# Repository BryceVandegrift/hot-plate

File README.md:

# PCB Hot Plate

A modular PCB soldering hot plate using only through hole components

## About

A modular PCB hot plate designed for hot plate soldering. It is designed for SMD
soldering and can go up to 180°C. Made using only through hole components in
order to make it easy to be built by hobbyists.

## Specifications

- 180°C max temperature
- Microcontroller: Atmel ATTINY84A
- Display: 128x64 pixel SSD1306 or compatible display
- Modular/interchangeable hot plates
- Support for simple heat curves
- 18-20 volt 2x5.5mm DC input
- 3 button input

Best used with low melt solder paste. This includes (but is not limited to):
- Sn48/In52
- Sn42/Bi58
- Sn42/Bi57/Ag1.0

## Usage

When you power up the hot plate you will be presented with 2 modes:

- Normal heating
- Heat curve

### Normal Heating

Normal heating mode is very simple to use. Just set a temperature and the hot
plate will heat up and stay at the set temperature. You can press `Enter` in
order to enter into cooling mode afterwards.

### Heat Curve

Heat curve mode lets you set and use your own custom heat curve. There are 5
parts to heat curve mode:

- Preheat: Temperature to preheat
- Soak: Amount of time (in seconds) to "soak" in preheat temperature
- Reflow heating: Temperature to reflow
- Reflow: Amount of time (in seconds) to reflow
- Cooldown

Pressing `Enter` will skip to the next stage of the heat curve.
Heat curve mode roughly follows this graph:

## Hardware

### Schematics

[Control Board Schematic](KiCAD/schematics/plate.pdf)

[Hot Plate Schematic](KiCAD/schematics/100x100-plate.pdf)

### Build Instructions

Please refer to the [Building Instructions](Build.md) page for detailed instructions.

### Connectors and Switches

#### J1 - DC Power Input

| Pin | Description   |
| --- | -----------   |
| 1   | +18-20V power |
| 2   | Ground        |
| 3   | Ground        |

#### J2 - ISCP Header

| Pin | Description  |
| --- | -----------  |
| 1   | MISO         |
| 2   | +5V          |
| 3   | SCL          |
| 4   | MOSI         |
| 5   | Reset        |
| 6   | Ground       |

#### J3 - Hot Plate Connector

| Pin | Description         |
| --- | -----------         |
| 1   | NC                  |
| 2   | +18-20V             |
| 3   | +18-20V             |
| 4   | MOSFET drain        |
| 5   | MOSFET drain        |
| 6   | +5V                 |
| 7   | Ground              |
| 8   | Temp. sensor output |

*Note: The J3 connector on the control board is exactly the same as the J1
connector on the hot plate board*

### Bill of Materials

A list of all Digikey parts can be found [here](https://www.digikey.com/en/mylists/list/93WA87OA5L)

#### Control Board

| Type               | Reference | Description                             | Quantity | Source                              |
| ----               | --------- | -----------                             | -------- | ------                              |
| Integrated Circuit | U1        | L7805CV voltage regulator               | 1        | Digikey 497-1443-5-ND               |
| Integrated Circuit | U2        | ATTINY84A-PU microcontroller            | 1        | Digikey ATTINY84A-PU-ND             |
| Display            | U3        | SSD1306 128x64 0.96" display            | 1        | Ebay, AliExpress, and other sources |
| IC Socket          | U2        | DIP-14 300 mil socket                   | 1        | Digikey ED3014-ND                   |
| Diode              | D1, D2    | SD103A                                  | 2        | Digikey SD103AVSCT-ND               |
| Diode              | D3        | 1N5231                                  | 1        | Digikey 1N5231B-ND                  |
| MOSFET             | Q1        | IRLZ44N                                 | 1        | Digikey IRLZ44NPBF-ND               |
| Capacitor          | C1        | 100uF, Electrolytic, 3.5mm lead spacing | 1        | Digikey 732-9187-1-ND               |
| Capacitor          | C2-C4, C8 | 0.1uF, MLCC, 5mm lead spacing           | 4        | Digikey BC2665CT-ND                 |
| Capacitor          | C5-C7     | 3300pF, MLCC, 2.5mm lead spacing        | 3        | Digikey BC1075CT-ND                 |
| Resistor           | R1-R5, R7 | 10kOhm, through hole                    | 6        | Digikey 13-MFR-25FRF52-10KCT-ND     |
| Resistor           | R6        | 30kOhm, through hole                    | 1        | Digikey 13-MFR-25FTE52-30KCT-ND     |
| Resistor           | R8        | 200Ohm, throught hole                   | 1        | Digikey 200XBK-ND                   |
| Tactile Button     | SW1-SW3   | 6mm tactile button                      | 3        | Digikey 450-1654-ND                 |
| DC Jack            | J1        | 2x5.5mm, through hole, right angle      | 1        | Digikey CP-002AH-ND                 |
| Pin Header         | J2        | 6 pin header, 2.54mm pitch, 2x3 pins    | 1        | Digikey 732-5394-ND                 |
| Pin Header         | J3        | 8 pin header, 2.54mm pitch, right angle | 1        | Digikey 2057-PH1RB-08-UA-ND         |

#### Hot Plate

| Type               | Reference | Description                             | Quantity | Source                             |
| ----               | --------- | -----------                             | -------- | ------                             |
| Integrated Circuit | U1        | LMT87LPGM temperature sensor            | 1        | Digikey 296-LMT87LPGMCT-ND         |
| Capacitor          | C1, C2    | 0.1uF, MLCC, 5mm lead spacing           | 2        | Digikey BC2665CT-ND                |
| Pin Socket         | J1        | 8 pin header, 2.54mm pitch, right angle | 1        | Digikey S5483-ND                   |

## License

Source code is licensed under the GPLV3 or later.

Everything else is licensed under the CERN-OHL-W-2.0.

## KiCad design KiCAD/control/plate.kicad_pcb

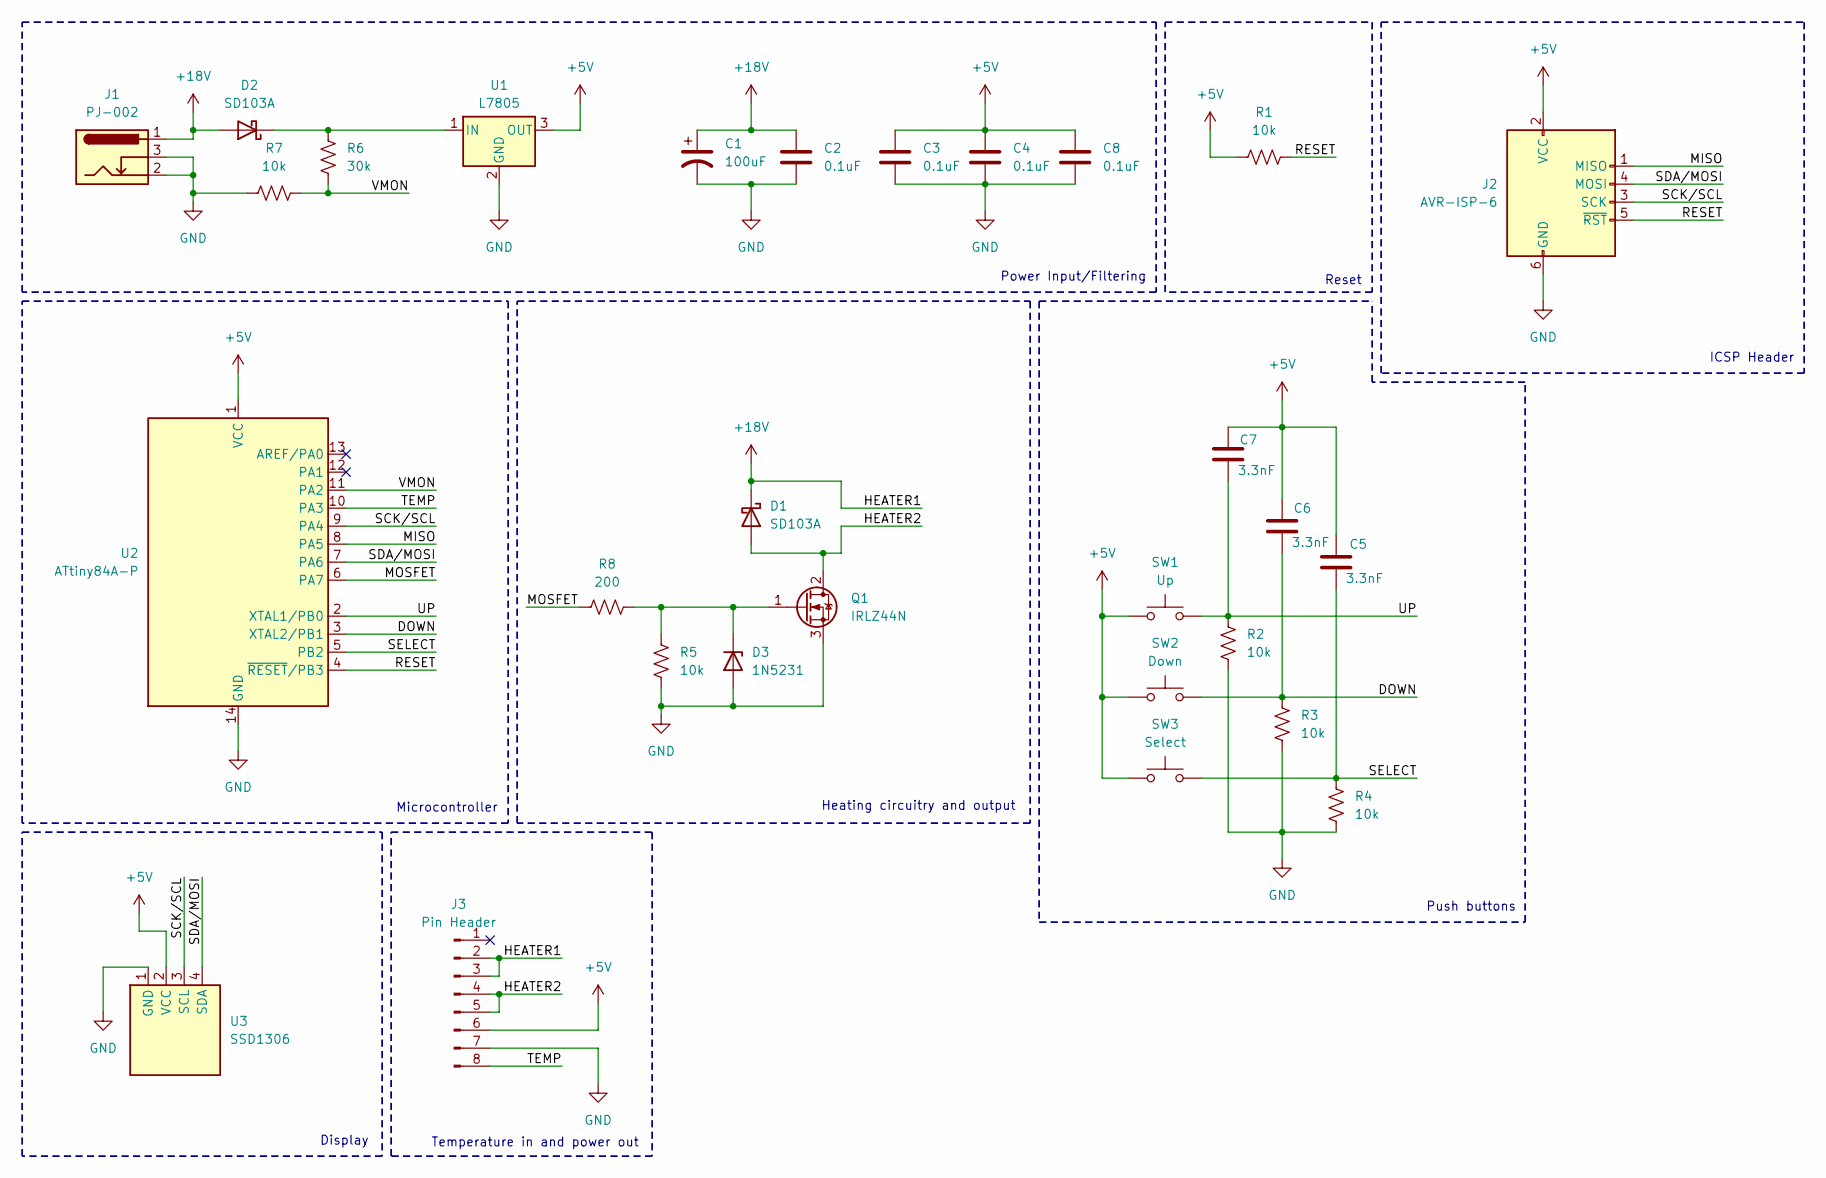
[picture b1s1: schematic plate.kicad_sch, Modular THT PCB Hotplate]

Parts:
C1: 100uF; CP_Radial_D8.0mm_P3.50mm
C2, C3, C4, C8: 0.1uF; C_Disc_D4.7mm_W2.5mm_P5.00mm
C5, C6, C7: 3.3nF; C_Disc_D3.8mm_W2.6mm_P2.50mm
D1, D2: SD103A; D_DO-35_SOD27_P7.62mm_Horizontal
D3: 1N5231; D_DO-35_SOD27_P7.62mm_Horizontal
J1: PJ-002; BarrelJack_Horizontal
J2: AVR-ISP-6; IDC-Header_2x03_P2.54mm_Vertical
J3: Pin Header; PinHeader_1x08_P2.54mm_Horizontal
Q1: IRLZ44N; TO-220-3_Horizontal_TabDown
R1, R2, R3, R4, R5, R7: 10k; R_Axial_DIN0207_L6.3mm_D2.5mm_P10.16mm_Horizontal
R6: 30k; R_Axial_DIN0207_L6.3mm_D2.5mm_P10.16mm_Horizontal
R8: 200; R_Axial_DIN0207_L6.3mm_D2.5mm_P10.16mm_Horizontal
SW1: Up; SW_PUSH_6mm_H7.3mm
SW2: Down; SW_PUSH_6mm_H7.3mm
SW3: Select; SW_PUSH_6mm_H7.3mm
U1: L7805; TO-220-3_Horizontal_TabDown
U2: ATtiny84A-P; DIP-14_W7.62mm_Socket
U3: SSD1306

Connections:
+5V: C3.1, C4.1, C5.1, C6.1, C7.1, C8.1, J2.2 (VCC), J3.6, R1.1, SW1.1, SW2.1, SW3.1, U1.3 (OUT), U2.1 (VCC), U3.2 (VCC)
+18V: C1.1, C2.1, D1.1 (K), D2.2 (A), J1.1, J3.2, J3.3
/DOWN: C6.2, R3.2, SW2.2, U2.3 (XTAL2/PB1)
/HEATER2: D1.2 (A), J3.4, J3.5, Q1.2 (D)
/MISO: J2.1 (MISO), U2.8 (PA5)
/MOSFET: R8.1, U2.6 (PA7)
/RESET: J2.5 (~RST), R1.2, U2.4 (~RESET/PB3)
/SCK/SCL: J2.3 (SCK), U2.9 (PA4), U3.3 (SCL)
/SDA/MOSI: J2.4 (MOSI), U2.7 (PA6), U3.4 (SDA)
/SELECT: C5.2, R4.2, SW3.2, U2.5 (PB2)
/TEMP: J3.8, U2.10 (PA3)
/UP: C7.2, R2.2, SW1.2, U2.2 (XTAL1/PB0)
/VMON: R6.1, R7.2, U2.11 (PA2)
GND: C1.2, C2.2, C3.2, C4.2, C8.2, D3.2 (A), J1.2, J1.3, J2.6 (GND), J3.7, Q1.3 (S), R2.1, R3.1, R4.1, R5.1, R7.1, U1.2 (GND), U2.14 (GND), U3.1 (GND)
unnamed: D2.1 (K), R6.2, U1.1 (IN)
unnamed: D3.1 (K), Q1.1 (G), R5.2, R8.2

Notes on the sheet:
Display
Heating circuitry and output
Push buttons
Power Input/Filtering
Temperature in and power out
Reset
ICSP Header
Microcontroller

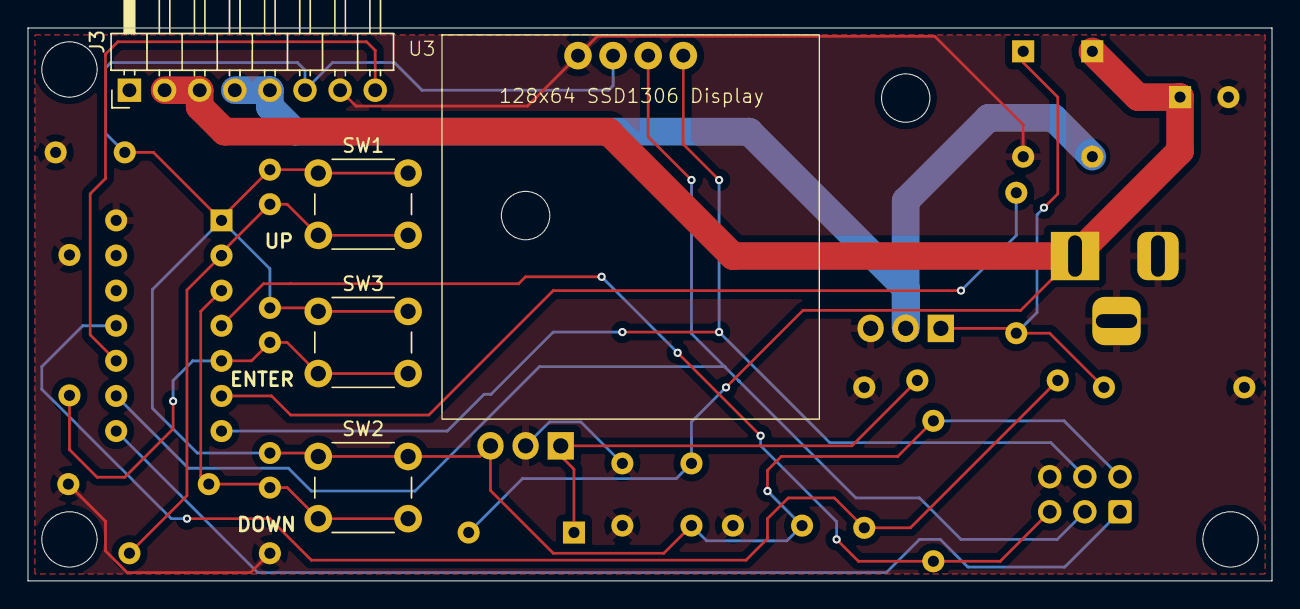
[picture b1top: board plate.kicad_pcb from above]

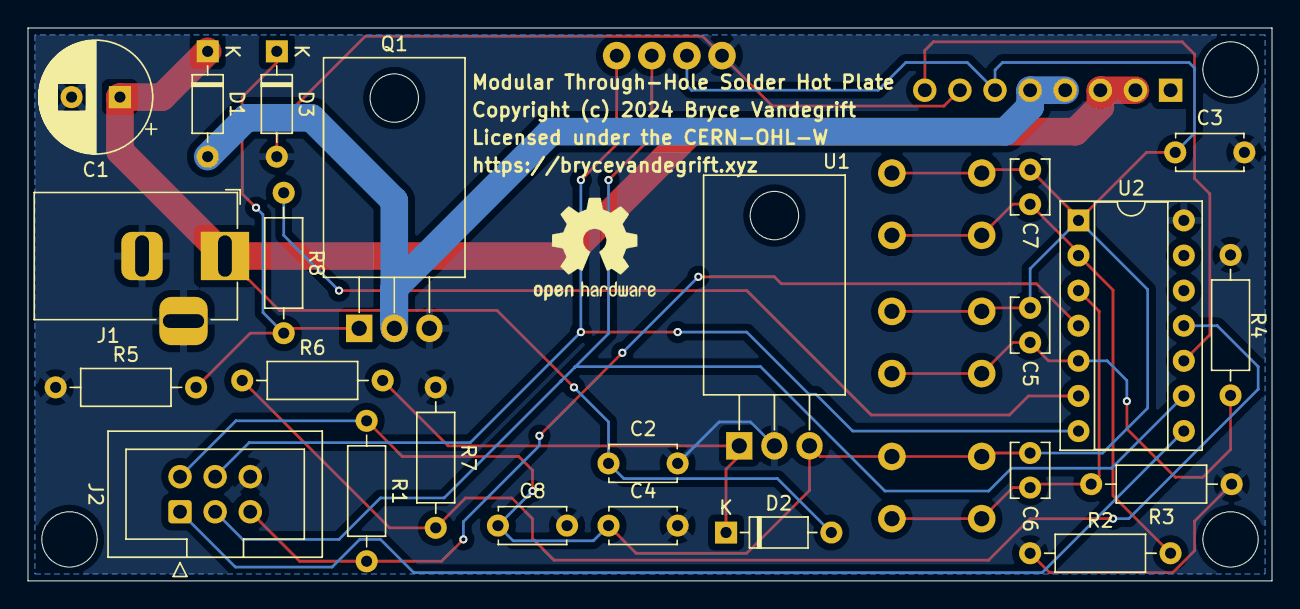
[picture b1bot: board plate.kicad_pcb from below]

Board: 2 copper layers, 90.0 x 40.0 mm, 29 parts (24 on the bottom side), 16 nets.

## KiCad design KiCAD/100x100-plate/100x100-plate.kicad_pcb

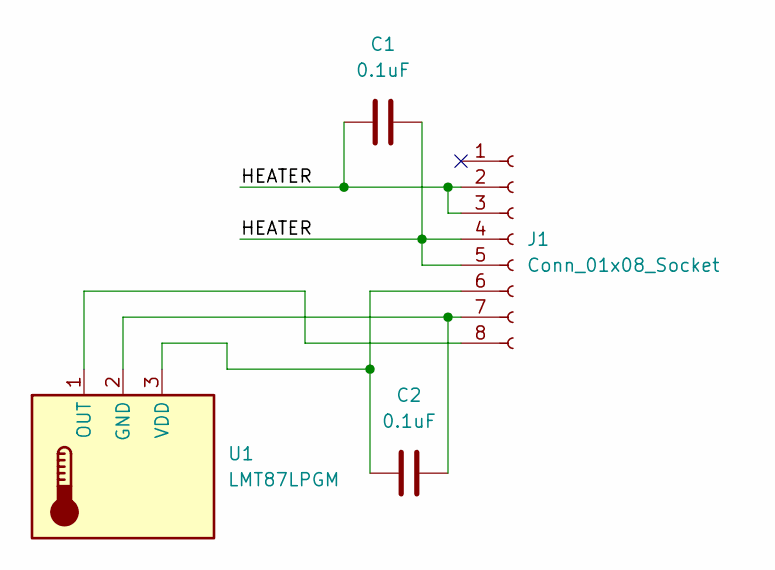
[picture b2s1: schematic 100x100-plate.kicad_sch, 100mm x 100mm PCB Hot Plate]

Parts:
C1, C2: 0.1uF; C_Disc_D4.7mm_W2.5mm_P5.00mm
J1: Conn_01x08_Socket; PinSocket_1x08_P2.54mm_Horizontal
U1: LMT87LPGM; TO-92Flat

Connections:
/HEATER: C1.1, C1.2, J1.2, J1.3, J1.4, J1.5
unnamed: C2.2, J1.6, U1.3 (VDD)
unnamed: C2.1, J1.7, U1.2 (GND)
unnamed: J1.8, U1.1 (OUT)

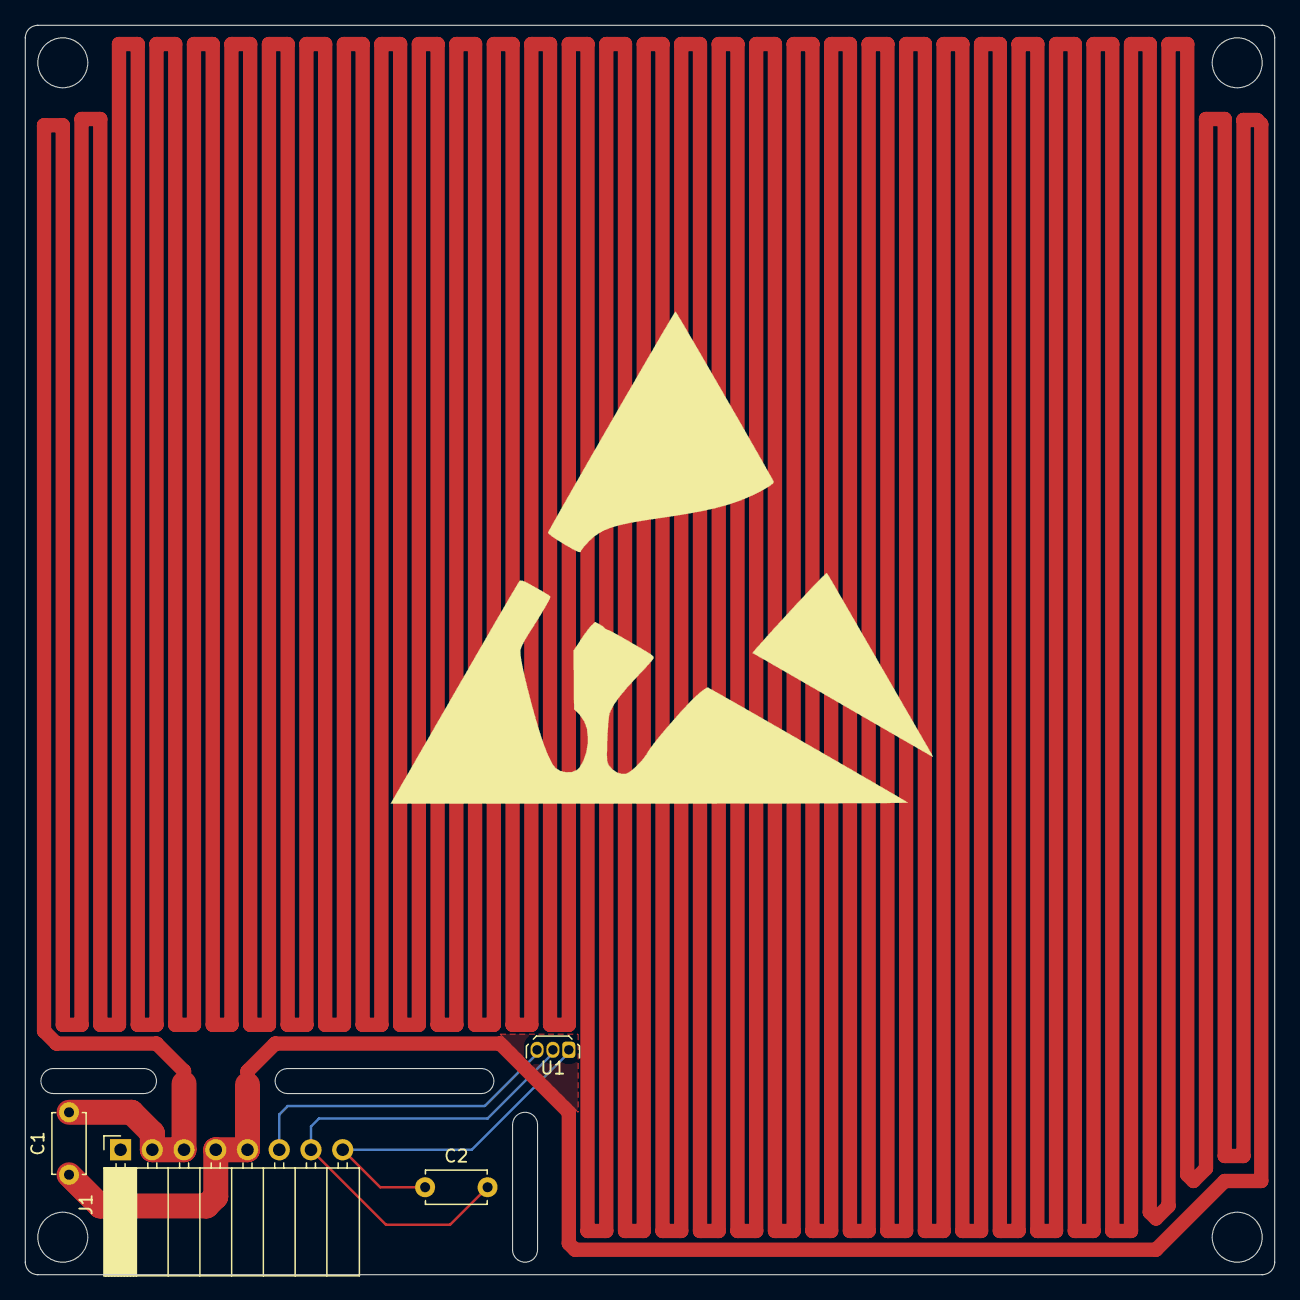
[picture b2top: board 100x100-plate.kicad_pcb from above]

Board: 2 copper layers, 100.0 x 100.0 mm, 4 parts (0 on the bottom side), 4 nets.

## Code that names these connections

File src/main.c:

/* See LICENSE for license details. */

#include <avr/eeprom.h>
#include <avr/io.h>
#include <util/delay.h>

#include "oled.h"

#define DEBOUNCE while((PINB & (1 << PINB0)) || (PINB & (1 << PINB1)) || (PINB & (1 << PINB2))) {}

#define MOSFET_ON PORTA |= (1 << PORTA7)
#define MOSFET_OFF PORTA &= ~(1 << PORTA7)

#define TEMP_ADDR 0x00
#define PREHEAT_ADDR 0x01
#define REFLOW_ADDR 0x02
#define SOAK_ADDR 0x03
#define LIQUID_ADDR 0x04

/* min and max temperatures */
#define MAX_TEMP 180
#define MIN_TEMP 50

/* min and max times for soak and reflow */
#define MAX_SOAK 250
#define MIN_SOAK 10
#define MAX_REFLOW 60
#define MIN_REFLOW 1
/* 2000 mV on ADC is around 6.5 V */
#define MIN_MV 2000

#define VERSION "Version 2.0"

static void setup(void);
static uint8_t analog_read(uint8_t pin);
static void int_to_str(char *s, uint16_t n);
static uint16_t read_temp(void);
static uint16_t read_volts(void);
static void cool(void);
static void heat(const char *msg, uint8_t set_temp, uint8_t stop);
static void hold(const char *msg, uint8_t set_temp, uint8_t set_sec);
static void set_var(const char *msg1, const char *msg2, uint8_t min, uint8_t max, uint8_t *var);
static void normal_mode(void);
static void curve_mode(void);

/* normal mode temperature */
static uint8_t temp = MIN_TEMP;
/* curve mode temperatures */
static uint8_t preheat = MIN_TEMP;
static uint8_t reflow = 100;
/* curve mode times */
static uint8_t soak = 30;
static uint8_t liquid = 10;

void
setup()
{
	uint8_t eeprom;

	/* Pinouts:
	 * PA0: Not connected
	 * PA1: Not connected
	 * PA2: Voltage monitor
	 * PA3: Temperature input
	 * PA4: Slave clock
	 * PA5: Not used (MISO)
	 * PA6: Slave data
	 * PA7: MOSFET output
	 *
	 * PB0: UP button input
	 * PB1: DOWN button input
	 * PB2: SELECT button input
	 * PB3: Not used (RESET)
	 */
	DDRA = 0xd0; /* 11010000 */
	DDRB = 0x00;

	PORTA = 0x50; /* 01010000 */
	PORTB = 0x00;

	/* enable power to ADC */
	PRR &= ~(1 << PRADC);

	/* use VCC as AREF */
	ADMUX &= ~((1 << REFS1) | (1 << REFS0));

	/* left justify ADC bits for clean 8-bit value */
	ADCSRB |= (1 << ADLAR);

	/* enable ADC on port A */
	ADCSRA |= (1 << ADEN);

	/* pull normal mode temp from eeprom */
	__EEGET(eeprom, TEMP_ADDR);
	if (eeprom >= MIN_TEMP && eeprom <= MAX_TEMP) {
		temp = eeprom;
	}

	/* pull heat curve mode variables */
	eeprom_busy_wait();
	__EEGET(eeprom, PREHEAT_ADDR);
	if (eeprom >= MIN_TEMP && eeprom <= MAX_TEMP) {
		preheat = eeprom;
	}

	eeprom_busy_wait();
	__EEGET(eeprom, REFLOW_ADDR);
	if (eeprom >= MIN_TEMP && eeprom <= MAX_TEMP) {
		reflow = eeprom;
	}

	eeprom_busy_wait();
	__EEGET(eeprom, SOAK_ADDR);
	if (eeprom >= MIN_SOAK && eeprom <= MAX_SOAK) {
		soak = eeprom;
	}

	eeprom_busy_wait();
	__EEGET(eeprom, LIQUID_ADDR);
	if (eeprom >= MIN_REFLOW && eeprom <= MAX_REFLOW) {
		liquid = eeprom;
	}
}

uint8_t
analog_read(uint8_t pin)
{
	ADMUX = ((ADMUX & 0xf0) | pin);

	ADCSRA |= (1 << ADSC);
	while (ADCSRA & (1 << ADSC));
	return ADCH;
}

void
int_to_str(char *s, uint16_t n)
{
	uint16_t i = 10000;
 
	while (i > n) i /= 10;

	do {
		*s++ = '0' + (((n - n % i) / i) % 10);
	} while (i /= 10);

	if (n < 100) {
		*s = ' ';
		s++;
	}

	*s = 0;
}

uint16_t
read_temp()
{
	uint8_t i;
	float data = 0;

	for (i = 0; i < 100; i++) {
		data += analog_read(PINA3);
	}

	data /= 100;
	data *= 19.53125; /* (5.0 / 256) * 1000 */
	return (uint16_t)((data - 2637) / -13.6);
}

uint16_t
read_volts()
{
	uint8_t i;
	float data = 0;

	for (i = 0; i < 20; i++) {
		data += analog_read(PINA2);
	}

	data /= 20;
	data *= 19.53125; /* (5.0 / 256) * 1000 */
	return (uint16_t)data;
}

void
cool()
{
	uint16_t rtemp;
	char buf[8];

	oled_clear();

	DEBOUNCE;

	oled_setpos(0, 0);
	oled_print("Cooling...");

	oled_setpos(0, 3);
	oled_print("Temp: ");

	for (;;) {
		oled_setpos(32, 3);
		rtemp = read_temp();
		int_to_str(buf, rtemp);
		oled_print(buf);

		if (PINB & (1 << PINB2)) {
			break;
		}

		_delay_ms(10);
	}
}

void
heat(const char *msg, uint8_t set_temp, uint8_t stop)
{
	uint16_t rtemp;
	char buf[8];

	oled_clear();

	DEBOUNCE;

	oled_setpos(0, 0);
	oled_print(msg);

	oled_setpos(0, 3);
	oled_print("Temp: ");

	for (;;) {
		oled_setpos(32, 3);
		rtemp = read_temp();
		int_to_str(buf, rtemp);
		oled_print(buf);

		if (read_volts() < MIN_MV) {
			goto undervolt;
		}

		if (rtemp < set_temp) {
			MOSFET_ON;
		} else {
			MOSFET_OFF;
		}

		if (PINB & (1 << PINB2)) {
			break;
		}

		/* if stop is set and target temp is reached, return */
		if (stop && rtemp >= set_temp) {
			return;
		}

		_delay_ms(10);
	}

	MOSFET_OFF;

	return;

undervolt:

	MOSFET_OFF;

	oled_clear();
	oled_setpos(0, 0);
	oled_print("Voltage is too low!");

	for (;;) {
		if (PINB & (1 << PINB2)) {
			break;
		}
	}
}

void
hold(const char *msg, uint8_t set_temp, uint8_t set_sec)
{
	uint16_t rtemp;
	char buf[8];
	uint8_t i;

	oled_clear();

	DEBOUNCE;

	oled_setpos(0, 0);
	oled_print(msg);

	oled_setpos(0, 2);
	oled_print("Time: ");

	oled_setpos(0, 3);
	oled_print("Temp: ");

	/*
	 * a simple (but inaccurate) alternative to using timers.
	 * works well enough I guess... 
	 */
	for (i = set_sec; i > 0; i--) {
		oled_setpos(32, 3);
		rtemp = read_temp();
		int_to_str(buf, rtemp);
		oled_print(buf);

		oled_setpos(32, 2);
		int_to_str(buf, i);
		oled_print(buf);

		if (read_volts() < MIN_MV) {
			goto undervolt;
		}

		if (rtemp < set_temp) {
			MOSFET_ON;
		} else {
			MOSFET_OFF;
		}

		if (PINB & (1 << PINB2)) {
			break;
		}

		_delay_ms(1000);
	}

	MOSFET_OFF;

	return;

undervolt:

	MOSFET_OFF;

	oled_clear();
	oled_setpos(0, 0);
	oled_print("Voltage is too low!");

	for (;;) {
		if (PINB & (1 << PINB2)) {
			break;
		}
	}
}

void
set_var(const char *msg1, const char *msg2, uint8_t min, uint8_t max, uint8_t *var)
{
	char buf[8];

	oled_clear();

	oled_setpos(0, 0);
	oled_print(msg1);

	oled_setpos(0, 3);
	oled_print(msg2);

	for (;;) {
		oled_setpos(64, 3);
		int_to_str(buf, *var);
		oled_print(buf);

		if (PINB & (1 << PINB0) && *var < max) {
			(*var)++;
		} else if (PINB & (1 << PINB1) && *var > min) {
			(*var)--;
		} else if (PINB & (1 << PINB2)) {
			return;
		}

		_delay_ms(100);
	}
}

void
normal_mode()
{
	oled_clear();

	DEBOUNCE;

	set_var("Set temperature", "Set temp:", MIN_TEMP, MAX_TEMP, &temp);

	/* write normal mode temp to eeprom */
	__EEPUT(TEMP_ADDR, temp);

	heat("Heating...", temp, 0);
	cool();
}

void
curve_mode()
{
	oled_clear();

	DEBOUNCE;

	set_var("Set preheat temp", "Set temp:", MIN_TEMP, MAX_TEMP, &preheat);
	set_var("Set soak time", "Set time:", MIN_SOAK, MAX_SOAK, &soak);
	set_var("Set reflow temp", "Set temp:", MIN_TEMP, MAX_TEMP, &reflow);
	set_var("Set reflow time", "Set time:", MIN_REFLOW, MAX_REFLOW, &liquid);

	/* write heat curve values to eeprom */
	__EEPUT(PREHEAT_ADDR, preheat);
	eeprom_busy_wait();
	__EEPUT(SOAK_ADDR, soak);
	eeprom_busy_wait();
	__EEPUT(REFLOW_ADDR, reflow);
	eeprom_busy_wait();
	__EEPUT(LIQUID_ADDR, liquid);

	heat("Preheating...", preheat, 1);
	hold("Soaking...", preheat, soak);
	heat("Heating to reflow...", reflow, 1);
	hold("Reflowing...", reflow, liquid);
	cool();
}

int
main()
{
	uint8_t cursor = 0;

	setup();

	_delay_ms(1000);

	oled_init();
	oled_clear();
	oled_setpos(0, 0);
	oled_print("PCB Hot Plate");
	oled_setpos(0, 3);
	oled_print(VERSION);
	_delay_ms(3000);

reset:
	oled_clear();

	oled_setpos(0, 0);
	oled_print("Select mode:");

	oled_setpos(8, 2);
	oled_print("Normal heating");

	oled_setpos(8, 3);
	oled_print("Heat curve");

	for (;;) {
		if (!cursor) {
			oled_setpos(0, 2);
			oled_print(">");
			oled_setpos(0, 3);
			oled_print(" ");
		} else {
			oled_setpos(0, 2);
			oled_print(" ");
			oled_setpos(0, 3);
			oled_print(">");
		}

		if (PINB & (1 << PINB0) || PINB & (1 << PINB1)) {
			cursor = !cursor;
		} else if (PINB & (1 << PINB2)) {
			if (cursor) {
				curve_mode();
			} else {
				normal_mode();
			}

			break;
		}

		_delay_ms(100);
	}

	goto reset;

	return 0;
}

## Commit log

2024-12-13 Add LICENSE
    Add CERN Open Hardware License Weakly reciprocal for PCB and 3D models
2024-12-16 Add README.md
    Add description of project, links, and BOM
2024-12-16 Add .gitignore and remove backups
2024-12-16 Add license information
    Add additional license information and add GPL V3 or later to source
    code
2024-12-19 Add build instructions and make a few minor changes
    Add build instructions, move software license, add a few more details
    to README.md, and remove note.txt
2024-12-19 Add schematics, .stl file, and .hex file
2024-12-19 Add instructions to flash firmware
    Also fix misspelling of ICSP
2024-12-26 Change references to screen resolution
    Change screen resolution from 128x32 to 128x64.
    Turns out screen resolution is *not* 128x32...oops.
2025-01-22 Add 3D printed rings to help secure legs
2025-04-22 Add .gitignore and add button debouncing
2025-05-07 Update board software to 2.0
    This version adds support for very simple heat curves in order to
    somewhat automate the soldering process.
2025-05-07 Update documentation for version 2.0
    Also fix a few bad typos
2025-08-03 Remove duplicate .gitignore

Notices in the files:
KiCAD/100x100-plate/100x100-plate.kicad_pcb:
Copyright (c) 2024 Bryce Vandegrift
